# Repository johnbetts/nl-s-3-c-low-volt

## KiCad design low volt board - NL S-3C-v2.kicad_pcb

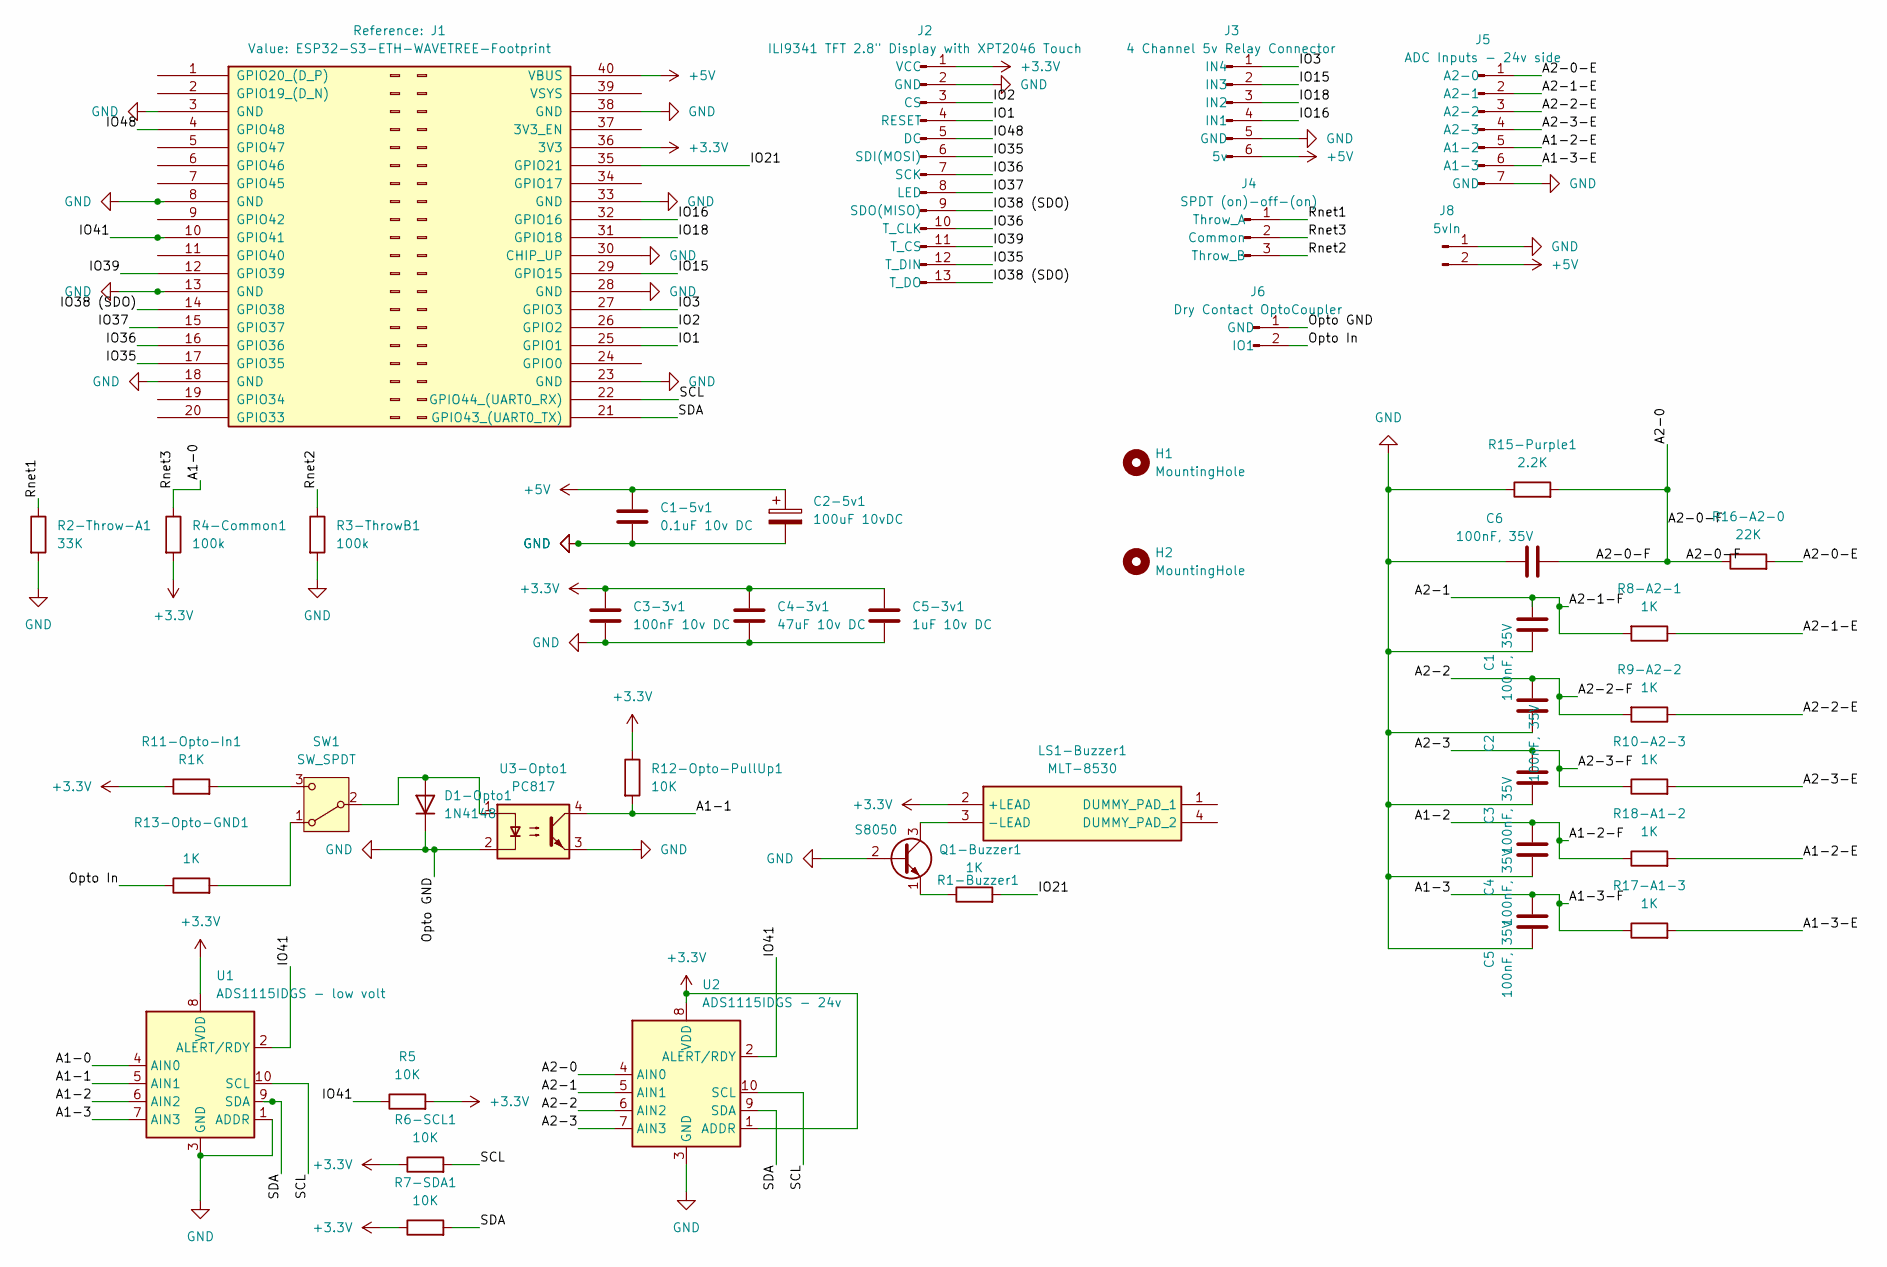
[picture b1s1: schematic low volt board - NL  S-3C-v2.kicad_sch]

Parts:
C1, C2, C3, C4, C5, C6: 100nF, 35V; C_0805_2012Metric
C1-5v1: 0.1uF 10v DC; C_0805_2012Metric
C2-5v1: 100uF 10vDC; C_0805_2012Metric
C3-3v1: 100nF 10v DC; C_0805_2012Metric
C4-3v1: 47uF 10v DC; C_0805_2012Metric
C5-3v1: 1uF 10v DC; C_0805_2012Metric
D1-Opto1: 1N4148; D_0805_2012Metric
H1, H2: MountingHole; MountingHole_4.3mm_M4_DIN965_Pad
J1: ESP32-S3-ETH-WAVETREE-Footprint; ESP32-PinHeader_2x20_P2.54mm_Vertical
J2: ILI9341 TFT 2.8" Display with XPT2046 Touch; PinHeader_1x13_P2.54mm_Vertical
J3: 4 Channel 5v Relay Connector; TerminalBlock_Phoenix_MKDS-1,5-6-5.08_1x06_P5.08mm_Horizont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
J4: SPDT (on)-off-(on); TerminalBlock_Phoenix_MKDS-1,5-3-5.08_1x03_P5.08mm_Horizont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
J5: ADC Inputs - 24v side; TerminalBlock_Phoenix_MKDS-1,5-7-5.08_1x07_P5.08mm_Horizont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
J6: Dry Contact OptoCoupler; TerminalBlock_Phoenix_MKDS-1,5-2-5.08_1x02_P5.08mm_Horizont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
J8: 5vIn; TerminalBlock_Phoenix_MKDS-1,5-2-5.08_1x02_P5.08mm_Horizont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
LS1-Buzzer1: MLT-8530; MLT8530; Manufacturer_Part_Number MLT-8530
Q1-Buzzer1: S8050; SOT-23
R1-Buzzer1, R8-A2-1, R9-A2-2, R10-A2-3, R13-Opto-GND1, R17-A1-3, R18-A1-2: 1K; R_0805_2012Metric
R2-Throw-A1: 33K; R_0805_2012Metric
R3-ThrowB1, R4-Common1: 100k; R_0805_2012Metric
R5, R6-SCL1, R7-SDA1, R12-Opto-PullUp1: 10K; R_0805_2012Metric
R11-Opto-In1: R1K; R_0805_2012Metric
R15-Purple1: 2.2K; R_0805_2012Metric
R16-A2-0: 22K; R_0805_2012Metric
SW1: SW_SPDT; SW_SPDT_Shouhan_MSK12C02
U1: ADS1115IDGS - low volt; TSSOP-10_3x3mm_P0.5mm
U2: ADS1115IDGS - 24v; TSSOP-10_3x3mm_P0.5mm
U3-Opto1: PC817; SOP-4_4.4x2.6mm_P1.27mm

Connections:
+3.3V: C3-3v1.1, C4-3v1.1, C5-3v1.1, J1.36 (3V3), J2.1 (VCC), LS1-Buzzer1.2 (+LEAD), R4-Common1.2, R5.2, R6-SCL1.1, R7-SDA1.1, R11-Opto-In1.1, R12-Opto-PullUp1.1, U1.8 (VDD), U2.1 (ADDR), U2.8 (VDD)
+5V: C1-5v1.1, C2-5v1.1, J1.40 (VBUS), J3.6 (5v), J8.2
/A1-0: J4.2 (Common), R4-Common1.1, U1.4 (AIN0)
/A1-1: R12-Opto-PullUp1.2, U1.5 (AIN1), U3-Opto1.4
/A1-2: C4.2, R18-A1-2.1, U1.6 (AIN2)
/A1-2-E: J5.5 (A1-2), R18-A1-2.2
/A1-3: C5.2, R17-A1-3.1, U1.7 (AIN3)
/A1-3-E: J5.6 (A1-3), R17-A1-3.2
/A2-0: C6.2, R15-Purple1.2, R16-A2-0.1, U2.4 (AIN0)
/A2-0-E: J5.1 (A2-0), R16-A2-0.2
/A2-1: C1.2, R8-A2-1.2, U2.5 (AIN1)
/A2-1-E: J5.2 (A2-1), R8-A2-1.1
/A2-2: C2.2, R9-A2-2.2, U2.6 (AIN2)
/A2-2-E: J5.3 (A2-2), R9-A2-2.1
/A2-3: C3.2, R10-A2-3.1, U2.7 (AIN3)
/A2-3-E: J5.4 (A2-3), R10-A2-3.2
/IO1: J1.25 (GPIO1), J2.4 (RESET)
/IO2: J1.26 (GPIO2), J2.3 (CS)
/IO3: J1.27 (GPIO3), J3.1 (IN4)
/IO15: J1.29 (GPIO15), J3.2 (IN3)
/IO16: J1.32 (GPIO16), J3.4 (IN1)
/IO18: J1.31 (GPIO18), J3.3 (IN2)
/IO21: J1.35 (GPIO21), R1-Buzzer1.2
/IO35: J1.17 (GPIO35), J2.6 (SDI(MOSI)), J2.12 (T_DIN)
/IO36: J1.16 (GPIO36), J2.7 (SCK), J2.10 (T_CLK)
/IO37: J1.15 (GPIO37), J2.8 (LED)
/IO38 (SDO): J1.14 (GPIO38), J2.9 (SDO(MISO)), J2.13 (T_DO)
/IO39: J1.12 (GPIO39), J2.11 (T_CS)
/IO41: J1.10 (GPIO41), R5.1, U1.2 (ALERT/RDY), U2.2 (ALERT/RDY)
/IO48: J1.4 (GPIO48), J2.5 (DC)
/Opto In: J6.2 (IO1), R13-Opto-GND1.1
/Rnet1: J4.1 (Throw_A), R2-Throw-A1.1
/Rnet2: J4.3 (Throw_B), R3-ThrowB1.1
/SCL: J1.22 (GPIO44_(UART0_RX)), R6-SCL1.2, U1.10 (SCL), U2.10 (SCL)
/SDA: J1.21 (GPIO43_(UART0_TX)), R7-SDA1.2, U1.9 (SDA), U2.9 (SDA)
GND: C1.1, C1-5v1.2, C2.1, C2-5v1.2, C3.1, C3-3v1.2, C4.1, C4-3v1.2, C5.1, C5-3v1.2, C6.1, D1-Opto1.1 (K), J1.3 (GND), J1.8 (GND), J1.13 (GND), J1.18 (GND), J1.23 (GND), J1.28 (GND), J1.30 (CHIP_UP), J1.33 (GND), J1.38 (GND), J2.2 (GND), J3.5 (GND), J5.7 (GND), J6.1 (GND), J8.1, Q1-Buzzer1.2 (B), R2-Throw-A1.2, R3-ThrowB1.2, R15-Purple1.1, U1.1 (ADDR), U1.3 (GND), U2.3 (GND), U3-Opto1.2, U3-Opto1.3
unnamed: D1-Opto1.2 (A), SW1.2 (B), U3-Opto1.1
unnamed: LS1-Buzzer1.3 (-LEAD), Q1-Buzzer1.3 (C)
unnamed: Q1-Buzzer1.1 (E), R1-Buzzer1.1
unnamed: R13-Opto-GND1.2, SW1.1 (A)
unnamed: R11-Opto-In1.2, SW1.3 (C)

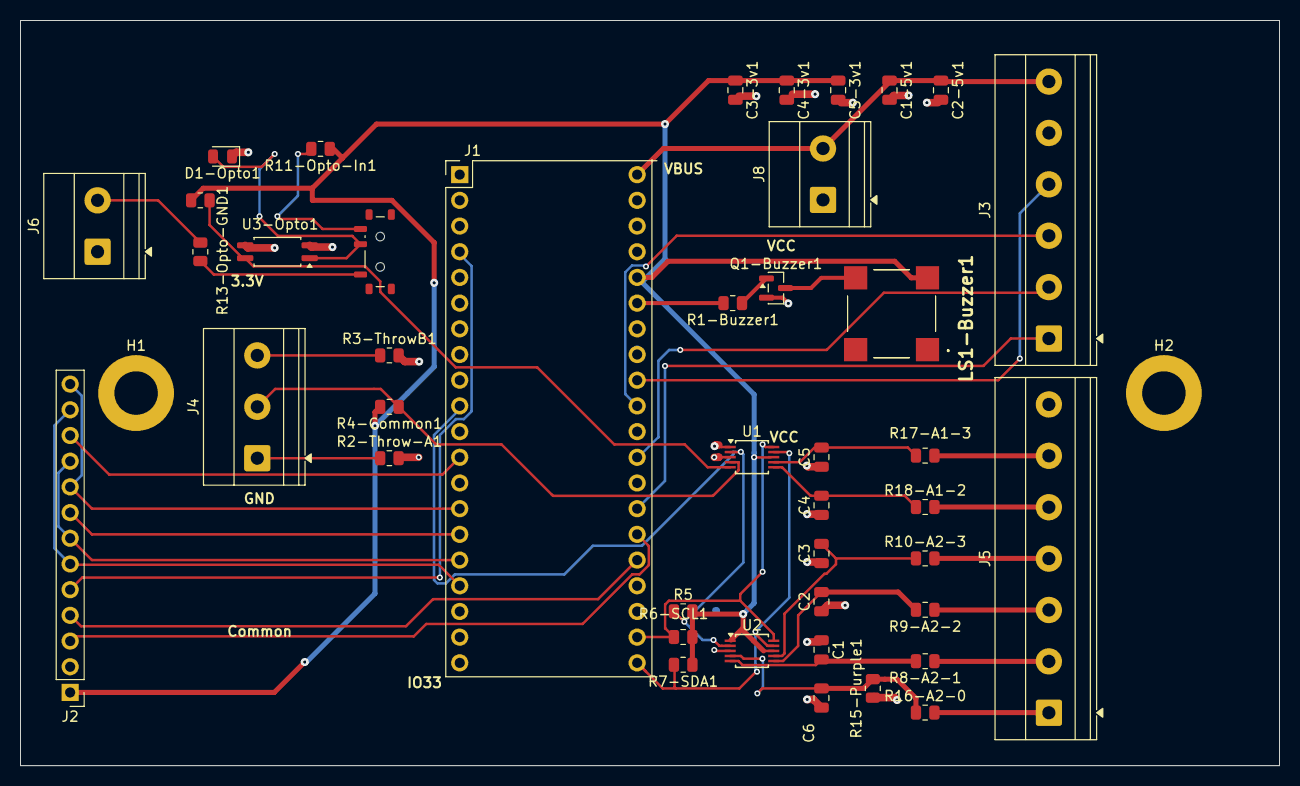
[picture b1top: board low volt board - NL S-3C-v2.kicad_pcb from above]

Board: 2 copper layers, 124.5 x 73.7 mm, 44 parts (0 on the bottom side), 41 nets.
